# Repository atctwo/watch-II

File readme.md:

# watch2

This repository contains the software and design files for my custom smartwatch thing.  The system is built on an ESP32, and the software is written in C++, using ESP-IDF and Arduino.  The software includes a few "apps", which are shown below.

The device uses a custom PCB that holds the ESP32, and all the other electronics that make the system work.  The PCB was designed in KiCad, and the enclosure for the device was made in OpenSCAD.

The system isn't as powerful as existing smartwatches, but it was a really great way for me to learn a lot of electronics and programming concepts and tools.  This isn't supposed to be a marketable product, but a proof of concept thing, and a way for me to develop my skills.  This repository is here as a kind of archive to show the level my skills are at at time of writing, and hopefully as a thing to look back on and learn from.

|  Watch Face            |  Settings           |  Calculator       | Stopwatch          |
|---------------------------------------------------|---------------------------------------------------|---------------------------------------------------|---------------------------------------------------|
|  Timer                 |  Alarms               |  File Browser   |  Notepad (read only) |
|  IR Remote         |  Image Viewer   |  Weather             |  Wikipedia         |
|  Quiz                   |  Music Player   |  Internet Radio        |  BLE Remote       |
|  Sensor Thing         |  Tetris                |  Snek 2                 |  NES |                                                   

# Project Structure

- `components` ESP-IDF components
- `design_files` KiCad files for the schematic and PCB
- `docs` documentation for the system (see `docs/readme.md` for more detail)
- `extras` other stuff like icons, data files, and pinout for the original breadboard prototype
- `main` where all the code lives
- `spiffs` data and images for the SPIFFS partition

# Build Instructions

These are some rough instructions for installing and flashing the software on to an ESP32 board.  These steps are mainly aimed for Linux systems.

1. make sure the latest commit of ESP-IDF is installed and setup (this software is currently using commit [1d7068e](https://github.com/espressif/esp-idf/tree/1d7068e4be430edd92bb63f2d922036dcf5c3cc1))
2. `git clone` this repository somewhere - `git clone https://github.com/atctwo/watch-II.git`
3. `cd` into the project directory
    - then run these commands:
    ```
    chmod +x install_libraries.sh
    ./install_libraries.sh
    ```
    - this script automatically clones all of the submodules that the system depends on, then makes any neccessary modifications
4. use `idf.py menuconfig` to tell ESP IDF the flash size of the ESP32 you are using
    - go to `Serial flasher config → Flash size` and select the right flash size (i've only created partition files for 8MB and 16MB at the minute)
    - go to `Partition table → Custom partition CSV file` and enter either `partitions_8mb.csv` or `partitions_16mb.csv`
5. to build the software, run `idf.py build`, and to write the built firmware to an ESP32 board, run `idf.py flash` (see the [ESP-IDF documentation](https://docs.espressif.com/projects/esp-idf/en/latest/esp32/api-guides/build-system.html#idf-py) for more detail on these commands)
6. next, flash an SPIFFS image to the device
    - to do that from the root of the repository, call one of these commands depending on what flash size your ESP32 has:
    ```bash
    # if you're using an 8 MB flash
    esptool.py --port /dev/ttyUSB0 write_flash 0x340000 spiffs/spiffs_8mb.bin  

    # if you're using a 16 MB flash
    esptool.py --port /dev/ttyUSB0 write_flash 0xE20000 spiffs/spiffs_16mb.bin  
    ```
    - more info on how SPIFFS is used can be found at [spiffs/readme.md](spiffs/readme.md)

# Credits
- *lots* of external libraries are used.  the details of these libraries can be found at [`docs/notes/libraries.md`](docs/notes/libraries.md)
- Most app icons are part of the [Papirus Icon Theme](https://github.com/PapirusDevelopmentTeam/papirus-icon-theme)
- Some icons made by [Icongeek26](https://www.flaticon.com/authors/icongeek26) from [Flaticon](https://www.flaticon.com/).
- The weather icons were designed by [Ian Amaral](https://dribbble.com/shots/5446697-Material-Design-inspired-weather-icons).
- The settings icon used in the IR Remote app is the one used by the Windows 10 Settings app.
- The icon used for the internet time button is [time zone](https://thenounproject.com/term/time-zone/2406165/) by Delwar Hossain from the Noun Project.
- The default font used is [HelvetiHand](https://www.dafont.com/helvetihand.font) by [Billy Snyder](https://www.dafont.com/billy-snyder.d4452).  It is modified slightly to add a ™ symbol.
- [Playing Cards](http://byronknoll.blogspot.com/2011/03/vector-playing-cards.html) by byronknoll

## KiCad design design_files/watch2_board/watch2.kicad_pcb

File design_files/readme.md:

# watch 2 Design Files

This folder has a few different subfolders, explained below.  The schematic and PCB for the watch were designed using KiCad.  All of the development on the current form of the schematic + PCB takes place in the `watch2_board` folder.  The case for the watch was designed in OpenSCAD, and was designed to be 3D printed.  The rest of the folders are kept for archival purposes.

- `projects_are_a_bad_idea` an old 1.27mm pitch ESP32 breakout board
- `watch2` an old proof-of-concept version of the watch2 board design 
- `watch2_board` the current version of the board design
- `watch2_case` the case for the watch

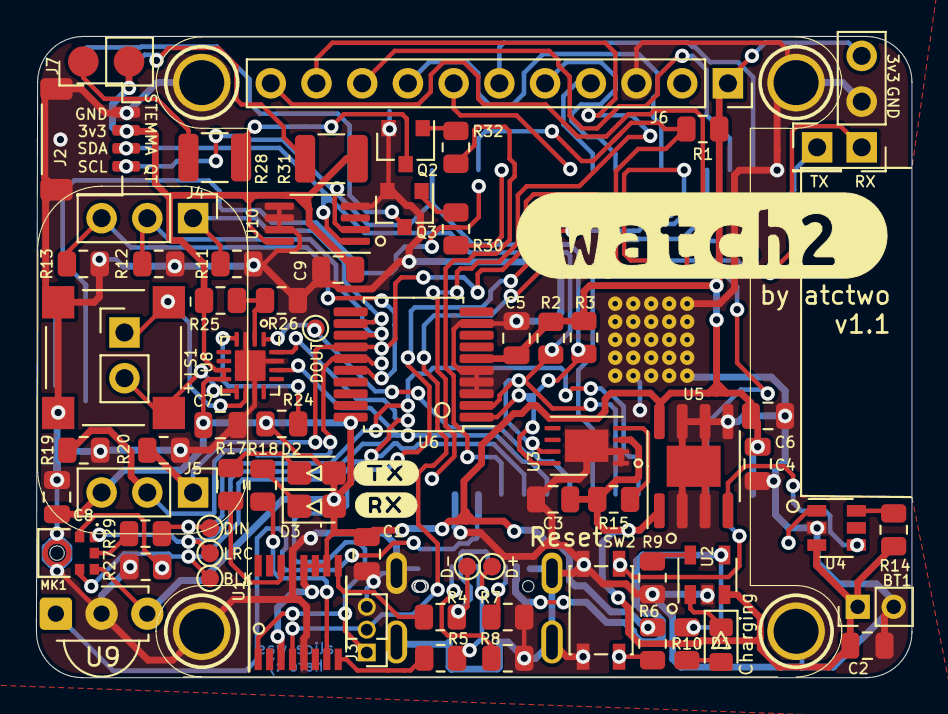
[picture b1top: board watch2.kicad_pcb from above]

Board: 2 copper layers, 48.6 x 35.6 mm, 78 parts (0 on the bottom side), 57 nets.

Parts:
BLK: TestPoint_Pad_D1.0mm
BT1: Battery_Cell; PinHeader_1x02_P2.00mm_Vertical
C1, C3, C5, C6, C7, C8, C9: 0.1uF; C_0805_2012Metric
C2, C4: 10uF; C_0805_2012Metric
D1: LED; LED_0805_2012Metric_Castellated
D2: TX; LED_0805_2012Metric_Castellated
D3: RX; LED_0805_2012Metric_Castellated
D5: LED_IR; SOD4223X290N
D+: TestPoint_Pad_D1.0mm
D-: TestPoint_Pad_D1.0mm
DIN: TestPoint_Pad_D1.0mm
DOUT: TestPoint_Pad_D1.0mm
IO0: Panasonic_EVQPUJ_EVQPUA
J1: USB_C_Receptacle_USB2.0; JAE_DX07S016JA1R1500
J2: STEMMA QT; JST_SH_SM04B-SRSS-TB_1x04-1MP_P1.00mm_Horizontal
J3: UART Connector; PinHeader_1x03_P1.27mm_Vertical
J4, J5: Conn_01x03_Male; PinHeader_1x03_P2.54mm_Vertical
J6: TFT Connector; PinSocket_1x11_P2.54mm_Vertical
J7: Torch Connector (main board); PinHeader_1x02_P2.54mm_Vertical
LRC: TestPoint_Pad_D1.0mm
LS1: Speaker; XDCR_CMT-7525-80-SMT-TR
MK1: SPH0645LM4H-B; MIC_SPH0645LM4H-B
Q2, Q3: Q_NPN_BCE; SOT-23
R1, R6, R10, R14, R17, R18: 1k; R_0805_2012Metric
R2, R3: 4k7; R_0805_2012Metric
R4, R5: 27R; R_0805_2012Metric
R7, R8: 5k1; R_0805_2012Metric
R9: 2k; R_0805_2012Metric
R11, R12, R13, R19, R20: R; R_0805_2012Metric
R15, R27: 10k; R_0805_2012Metric
R24: 680k; R_0805_2012Metric
R25, R26: 100k; R_0805_2012Metric
R28, R31: 100R; R_1210_3225Metric
R29: 68R; R_0805_2012Metric
R30, R32: 330R; R_0805_2012Metric
SW2, SW2#2: SW_Push; SW_SPST_EVQP2
SW3: Power Button; SW_SPST_EVQP2
Speaker: PinHeader_1x02_P2.54mm_Vertical
U1: FT230XS; SSOP-16_3.9x4.9mm_P0.635mm
U2: MCP73831-2-OT; SOT-23-5
U3: LC709203FQH-01TWG; WDFN-8-1EP_4x3mm_P0.65mm_EP2.4x1.8mm
U4: MAX16150AUT+T; SOT-23-6
U5: MAX604; SOIC-8-1EP_3.9x4.9mm_P1.27mm_EP2.29x3mm
U6: MCP23008-xSS; SSOP-20_5.3x7.2mm_P0.65mm
U7: ESP32-WROVER
U8: MAX98357AETE+T; QFN-16-1EP_3x3mm_P0.5mm_EP1.7x1.7mm
U9: TSOP38238; Vishay_MINICAST-3Pin
U10: MCP9808_MSOP; MSOP-8_3x3mm_P0.65mm
U$7, U$8, U$9, U$10: MOUNTINGHOLE2.5; MOUNTINGHOLE_2.5_PLATED

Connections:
+3V3: C1.1, C4.1, C5.1, C6.1, C7.1, C8.1, C9.1, D2.2, D3.2, J2.2, J5.3, J6.1, J7.2, MK1.5, R1.1, R2.1, R3.1, R6.1, R24.1, R25.1, R31.2, U1.3, U1.10, U1.11, U1.12, U5.8, U6.6, U6.20, U7.2, U8.7, U8.8, U9.3, U10.8
+5V: BT1.1, C2.1, C3.1, R14.1, R15.1, U2.3, U3.3, U4.3, U5.1
DPAD_DOWN: J5.2, R19.1, U6.15
DPAD_ENTER: J5.1, R20.1, U6.14, U7.4
DPAD_LEFT: J4.3, R13.1, U6.16
DPAD_RIGHT: J4.1, R11.1, U6.12
DPAD_UP: J4.2, R12.1, U6.13
ESP_EN: R6.2, SW2.1, SW2#2.1, U7.3
ESP_IO0: IO0.1, R1.2, U7.25
ESP_RX: J3.1, U1.1, U7.34
ESP_TX: J3.2, U1.4, U7.35
GND: BT1.2, C1.2, C2.2, C3.2, C4.2, C5.2, C6.2, C7.2, C8.2, C9.2, IO0.2, J1.S1, J1.S4, J2.1, J2.MP, J3.3, J6.3, MK1.3, Q2.2, Q3.2, R7.1, R8.1, R9.2, R11.2, R12.2, R13.2, R19.2, R20.2, R26.2, R27.1, SW2.2, SW2#2.2, SW3.2, U1.5, U1.13, U2.2, U3.1, U3.2, U3.9, U4.2, U5.2, U5.3, U5.5, U5.6, U5.7, U6.3, U6.4, U6.5, U6.9, U7.1, U7.15, U7.38, U7.39, U8.3, U8.11, U8.15, U8.17, U9.2, U10.4, U10.5, U10.6, U10.7, U$7.P$1, U$8.P$1, U$9.P$1, U$10.P$1
I2C_SCL: J2.4, R3.2, U3.8, U6.1, U7.23, U10.2
I2C_SDA: J2.3, R2.2, U3.7, U6.2, U7.8, U10.1
I2S_BLK: BLK.1, MK1.4, U7.12, U8.16
I2S_DIN: DIN.1, R29.2, U7.7
I2S_DOUT: DOUT.1, U7.10, U8.1
I2S_LRC: LRC.1, MK1.1, U7.11, U8.14
IR_RECV: U7.14, U9.1
LED_IR: R30.2, U7.26
LED_TORCH: R32.2, U7.13
unnamed: D1.1, U2.1
unnamed: D1.2, R10.1
unnamed: D2.1, R17.1
unnamed: D3.1, R18.1
unnamed: D5.1, Q3.3
unnamed: D5.2, R31.1
unnamed: R10.2, U2.4
unnamed: J7.1, R28.1
unnamed: LS1.1, LS1.N, Speaker.1, U8.10
unnamed: LS1.2, LS1.P, Speaker.2, U8.9
unnamed: MK1.2, R27.2
unnamed: MK1.6, R29.1
unnamed: Q2.1, R32.1
unnamed: Q2.3, R28.2
unnamed: Q3.1, R30.1
unnamed: R4.1, U1.9
unnamed: R5.1, U1.8
unnamed: R9.1, U2.5
unnamed: R14.2, U4.6
unnamed: R15.2, U3.4
unnamed: R17.2, U1.14
unnamed: R18.2, U1.7
unnamed: R24.2, U8.4
unnamed: R25.2, R26.1, U8.2
unnamed: SW3.1, U4.1
unnamed: U4.4, U5.4
SD_CS: J6.10, U7.16
TFT_BL: J6.11, U7.9
TFT_CLOCK: J6.4, U7.30
TFT_CS: J6.7, U7.29
TFT_DC: J6.9, U7.36
TFT_MISO: J6.5, U7.31
TFT_MOSI: J6.6, U7.37
TFT_RESET: J6.8, U7.33
USB_D+: D+.1, J1.6, J1.7, R5.2
USB_D-: D-.1, J1.5, J1.8, R4.2

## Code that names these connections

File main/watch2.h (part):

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#define tftbl 33        //tft backlight
#define tftbl_resolution 8 //resolution of backlight pwm in bits

#define dpad_up             1
#define dpad_down           3
#define dpad_left           4
#define dpad_right          0
#define dpad_enter          2
#define BATTERY_DIVIDER_PIN 34
#define TORCH_PIN           14
#define IR_SEND_PIN         4
#define IR_REC_PIN          12
#define I2S_DOUT            25
#define I2S_DIN             35
#define I2S_BCLK            27
#define I2S_LRC             26
#define I2C_SDA             32
#define I2C_SCL             15
#define SHUTDOWN_PIN        7 // mcp23008

//ledc channels
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#define KEY_REPEAT_DELAY    700     //time for key repeat to start, in ms [DAS]
#define KEY_REPEAT_PERIOD   50      //time between key repeats, in ms     [ARR]

#define dpad_up_active()    watch2::dpad_active(dpad_up)
#define dpad_down_active()  watch2::dpad_active(dpad_down)
#define dpad_left_active()  watch2::dpad_active(dpad_left)
#define dpad_right_active() watch2::dpad_active(dpad_right)
#define dpad_enter_active() watch2::dpad_active(dpad_enter)
#define dpad_any_active()   ( dpad_up_active() || dpad_down_active() || dpad_left_active() || dpad_right_active() || dpad_enter_active() )

#define draw(conditions, ...)                                       \      
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
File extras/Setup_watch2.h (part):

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#define TFT_INVERSION_ON
// #define TFT_INVERSION_OFF

// If a backlight control signal is available then define the TFT_BL pin in Section 2
// below. The backlight will be turned ON when tft.begin() is called, but the library
// needs to know if the LEDs are ON with the pin HIGH or LOW. If the LEDs are to be
// driven with a PWM signal or turned OFF/ON then this must be handled by the user
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// The DC (Data Command) pin may be labeled AO or RS (Register Select)
//
// With some displays such as the ILI9341 the TFT CS pin can be connected to GND if no more
// SPI devices (e.g. an SD Card) are connected, in this case comment out the #define TFT_CS
// line below so it is NOT defined. Other displays such at the ST7735 require the TFT CS pin
// to be toggled during setup, so in these cases the TFT_CS line must be defined and connected.
//
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// ###### EDIT THE PIN NUMBERS IN THE LINES FOLLOWING TO SUIT YOUR ESP8266 SETUP ######

// For NodeMCU - use pin numbers in the form PIN_Dx where Dx is the NodeMCU pin designation
//#define TFT_CS   PIN_D8  // Chip select control pin D8
//#define TFT_DC   PIN_D3  // Data Command control pin
//#define TFT_RST  PIN_D4  // Reset pin (could connect to NodeMCU RST, see next line)
//#define TFT_RST  -1    // Set TFT_RST to -1 if the display RESET is connected to NodeMCU RST or 3.3V

//#define TFT_BL PIN_D1  // LED back-light (only for ST7789 with backlight control pin)

//#define TOUCH_CS PIN_D2     // Chip select pin (T_CS) of touch screen

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//#define TFT_SPI_OVERLAP

// In ESP8266 overlap mode the TFT chip select MUST connect to pin D3
//#define TFT_CS   PIN_D3
//#define TFT_DC   PIN_D5  // Data Command control pin
//#define TFT_RST  PIN_D4  // Reset pin (could connect to NodeMCU RST, see next line)
//#define TFT_RST  -1  // Set TFT_RST to -1 if the display RESET is connected to NodeMCU RST or 3.3V

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// For ESP32 Dev board (only tested with ILI9341 display)
// The hardware SPI can be mapped to any pins

#define TFT_MISO 19
#define TFT_MOSI 23
#define TFT_SCLK 18
#define TFT_CS    5  // Chip select control pin
#define TFT_DC   22  // Data Command control pin
#define TFT_RST  21  // Reset pin (could connect to RST pin)
//#define TFT_RST  -1  // Set TFT_RST to -1 if display RESET is connected to ESP32 board RST

#define TFT_BL   17  // LED back-light (only for ST7789 with backlight control pin)

//#define TOUCH_CS 21     // Chip select pin (T_CS) of touch screen

//#define TFT_WR 22    // Write strobe for modified Raspberry Pi TFT only

// For the M5Stack module use these #define lines
//#define TFT_MISO 19
//#define TFT_MOSI 23
//#define TFT_SCLK 18
//#define TFT_CS   14  // Chip select control pin
//#define TFT_DC   27  // Data Command control pin
//#define TFT_RST  33  // Reset pin (could connect to Arduino RESET pin)
//#define TFT_BL   32  // LED back-light (required for M5Stack)

// ######       EDIT THE PINs BELOW TO SUIT YOUR ESP32 PARALLEL TFT SETUP        ######

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//#define ESP32_PARALLEL

// The ESP32 and TFT the pins used for testing are:
//#define TFT_CS   33  // Chip select control pin (library pulls permanently low
//#define TFT_DC   15  // Data Command control pin - must use a pin in the range 0-31
//#define TFT_RST  32  // Reset pin, toggles on startup

//#define TFT_WR    4  // Write strobe control pin - must use a pin in the range 0-31
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
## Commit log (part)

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2019-07-23 idk what i am doing
2019-07-23 is this how github works??
2019-07-24 Added theme colour stuff and clear settings mode
2019-07-25 Added hidden attribute for states
2019-07-26 Added scientific functions to calculator
2019-08-10 Fixed .gitigonre
2019-08-14 Added timer program
2019-08-17 Added alarms
2019-08-20 Fixed alarms and sleeping over two days
    Whenever an alarm was set for the next day, and the alarm went off, the
    current time would be later than the alarm time, but the alarm would
    not be paused. This meant that the time until the alarm goes off would
    evaluate as a negative number, and the device would instantly wake up
    when going into sleep. This commit changes the code so that the timer
    wakeup is only set if the alarm time is later than the current time.
2019-11-22 Added preliminary SD support
    - added light mode to top thing
    - top thing shows sd card mount status
    - added functions to handle mounting an sd card (initSD()) and to read
    the contents of a directory
    - initSD() is called at system startup, when the device is woken up, and
    when the user presses left on the watch face
2019-12-17 Added file selection dialogue - added a file selection dialogue, which allows the user to pick a file on the sd card - added design files for mainboard
2019-12-18 Rewrote state machine - states are now stored in an std::vector<stateMeta> instead of an std::map<int, stateMeta> (where stateMeta is a struct storing state details) - the states vector is now popula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
2019-12-27 started ir remote - added ir remote that loads ir remote profiles from sd card - sd card support is kind of broken, so the ir app is also kind of broken (it's wip) - it loads profiles stored on the s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
2019-12-31 global variables have been moved to a namespace all of the global variables used by the system have been moved to a namespace (watch2). this was done to hopefully improve organisation of code
2020-01-02 updated code to address members of watch2 directly most of the code in the last commit referenced members of the namespace watch2 indirectly (by using "using namespace watch2;"). the code has updated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
2020-01-09 state menu updated to work w/ tft
    - the state menu now looks ok on the tft
    - state icons have been redesigned, but i was too bored or lazy so
    they don't look very good, and will probably be re-redesigned
    later
    - updated ir remote so that you can actually pick an ir profile. it's
    still quite buggy
2020-01-16 added setFont function there is now a function to set the font, so you don't have to manually check if it exists
2020-01-17 updated stopwatch + wip framebuffer - the stopwatch now works with the tft - some code for an experimental framebuffer has added, but it doesn't work very well
2020-02-19 broke ir remote - broke the ir remote app. i'm going to rewrite it from scratch - i tried to add support for an ir receiver, but it's also broken
2020-03-04 updated alarm + timer complete screens - updated the time up screens for the timer and alarm apps to work with the tft
2020-05-08 i did a lot of things, are you proud of me? - added boot sequence step descriptions over serial (so you can see what's happening when the watch is booting) - removed the #include for Adafruit ImageRe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
2020-05-14 fixed new AP timeout issue
2020-05-16 made wiki app more reliable fixed a few bugs in the wikipedia app. it is ok at retrieving and parsing small articles (most of the time) but it fails catastrophically when handling large articles
2020-05-20 added experimental bluetooth support there is some very basic bluetooth support that enables a BLE HID keyboard using the BleKeyboard Arduino library. it doesn't do anything yet because you can't run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
2020-05-20 updated libraries list
2020-05-27 added wifi profile code to branch
2020-05-27 Updated CMakeLists.txt to fix a few compilation errors
2020-05-27 update ntp code?
2020-05-27 Fixed #18 (screen fading)
2020-05-28 fixed #20
2020-05-28 fixed #11
2020-05-28 ble kind of works - modified sdkconfig to disable BT classic, which means that BLE sort of works (idk why) - updated ripoff control centre so that the BT icon changes when the BT state changes - fixe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
2020-05-29 added integer image scaling
2020-05-29 fixed #22 (ntp ignores timezone)
2020-05-30 added i2s audio test
2020-06-08 added interfaces for different audio formats + fixed watch not waking up after sleep (#26)
2020-07-17 fixed some issues with drawing images
2020-07-20 added basic message box function
2020-07-28 updated IRRemote library + updated ir receiver - updated the system to use the latest version of the Arduino IRRemote library. The system previously used a fork of the library that added esp32 send s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
2020-07-30 (finally) added serial ir thing
2020-07-31 rolled IR library back to fork the latest upstream version of the library breaks IR sending for ESP32 devices
2020-07-31 help git is difficult
2020-08-01 fixed a bug that broke blank IR buttons this commit stops blank IR buttons mirroring button 0
2020-08-02 blank IR buttons don't do anything anymore
2020-08-04 added tetris app - added a tetris app based on the tetris engine i wrote a while ago - added tetris icon and tetris logo - menus can now have centred text
2020-08-05 removed docs
2020-08-05 turns display off when system sleeps; closes #8
2020-08-14 updated system to esp-idf-v4.0.1 and added jtag pins to pinout
2020-09-27 more attempting to get music stuff working
2020-10-01 the control centre now shows the weather! - it uses the openweather api - the key for the api is loaded from SPIFFS using a new key loading system - fixed a bug where wifi broke after disabling it - 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
    aaaaaaaaaaaaaaaaaaaaaaaaaaaaa
    i need to sleep 🙃
2020-10-01 added an interface to the quiz app - you can select a category and the difficulty, and questions and answers will be drawn on screen - you can't answer the question yet - the location used for the we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
2020-10-02 added NTP button to control centre
2020-10-26 added weather app it's not finished yet, it only shows the weather conditions for the next 7 days also, system icons can now be bmp or png
2020-10-26 added experimental nes emulator, using agnes
2020-11-03 added specific weather info for each day the weather app now shows more detailed weather info when you select a specific day
2020-11-09 sd test is now a file browser is shows you lots of file info like size and times, and you can rename or delete files and i am very tired
2020-11-11 fixed cmake error
2020-11-11 updates to music player
2020-11-18 added internet radio
2020-11-19 added sounds to alarms and timers and fixed a bug where leaving timer and alarm screens would hang the system?
2020-11-20 added method of changing alarm and timer sounds and updated alarm and timer icons
2020-11-22 images are now drawn using dma also, everything now uses arduino's SD library, rather than SdFat, because DMA image drawing seemed to break SdFat for some reason
2020-12-05 added watch face shortcuts
2021-01-05 i did a lot of things - fixed crash when loading games with the nes app - added new pcb that isn't finished yet - pinout changes?
2021-01-06 fixed #45 (sd doesn't work after sleep) and updated documentation on IRRemote modifications
2021-01-10 added linguist settings
2021-01-26 added nofrendo
2021-01-29 more nes stuff
2021-02-03 updated library documentation also, removed dependancy on SdFat
2021-02-03 added a library setup script also modified the libraries documentation to talk about this script
2021-02-03 added compiler flag to ESP32-audioI2S
2021-02-03 fixed syntax error?
2021-02-03 Added GitHub Actions action (#46)
    * added initial github actions test
    * fixed syntax error?
    * fixed job name
    * hi
2021-02-03 github actions fix?
2021-02-03 changed workflow to use the right checkout thing
2021-02-03 added step to update esp-idf submodules
2021-02-04 ble: added ble hid support to system previously, i was using T-vK's ESP32 BLE Keyboard library (https://github.com/T-vK/ESP32-BLE-Keyboard) to send media key reports over BLE. now, the system impleme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
2021-02-06 refactored ble functions they now have a nice api :)
2021-02-07 added audio recorder app it doesn't actually record any data yet, it just visualises it
2021-02-08 switched states to use header files now, instead of states.cpp including each of the cpp state files, the state files are compiled separately, and each of the state functions are declared in a separa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
2021-02-08 fixes to audio subsystem the i2s driver is now installed and uninstalled as needed
2021-02-09 removed Seeed Linechart dependancy
2021-02-09 more heap spring cleaning
2021-02-10 upgraded system to espidf v4.3 beta 1
2021-02-10 moved memory and task info to separate functions
2021-02-10 changed name of espidf workflow
    i accidentally forgot to change the name of the ESPIDF workflow when I switched from using v4.0.1 to v4.3-beta1
2021-02-12 created watch2 pcb it's mostly populated and wired up. i haven't checked it yet, and i haven't figured out how to make IO0 externaly pressable yet :)
2021-03-08 - switched BLE subsystem to NimBLE (from Bluedroid) using https://github.com/h2zero/esp-nimble-cpp/tree/master - renamed arduino-esp32 component to arduino - increased stack size + task priority for 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
2021-05-04 added 8mb partition file + spiffs data - added partition file for 8mb flash chips, and renamed existing one to partitions_16mb.csv - added folder to store stuff needed for spiffs - data folder contai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
2021-05-04 re-enabled quiz and nes emulator
2021-05-05 changed Serial.print callls to ESP_LOG calls the idea is that by setting a lower log level, the compiler will ignore _a lot_ of debug text, saving flash space
2021-05-05 added initial mcp9808 support
2021-05-05 added boot screen
2021-05-05 fixed #57 and #2
2021-05-06 fixed #49
2021-05-06 fixed #68
2021-05-07 added track info to music player + radio the music player now shows ID3 tag info, and the radio now shows station name and stream title
2021-05-07 fixed #47
2021-06-10 updated esp-idf + arduino + irremote each of these have been updated to latest
2021-06-11 added send + receive support for lots of protocols specifically non-AC protocols
2021-06-11 improved build instructions in readme
2021-06-30 i did some things - the commit which added LC709203F support didn't actually add anything, so this commit adds those things - some changes to Wifi logging
2021-06-30 actually added sensor thing the last commit didn't actually stage any files
2021-06-30 updated tetris app fixed a memory allocation bug and changed the block outline colour
2021-07-02 Added + updated some icons - finally fixed watch face icon - added sensors, snake, and cards icons
2021-07-02 Fixed image corruption The function that draws images to the TFT used to use DMA, but for some reason, the images got corrupted very easily. This commit switches to using the standard blocking non-DM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
2021-07-04 some tiny wifi changes
2021-07-04 Hopefully fixed Wifi after sleep bug!
2021-08-11 added a reddit app - added a reddit client that mostly works - added function to decode image from memory - battery is now read when watch starts - fixed quiz app? - some memory optimisations
2021-08-12 added ds1337 part 2
2021-08-14 fixed ir remote bug and made some memory optimisations
2021-08-14 added pcb v2 files again
2021-08-14 added watch2 case / enclosure
2021-08-14 added image of watch
2021-08-14 reset linguist part 2
2021-09-27 watch face optimisations :)

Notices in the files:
main/watch2.h:
@copyright Copyright (c) 2020 atctwo
